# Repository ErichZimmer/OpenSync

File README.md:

# OpenSync
An open source synchronizer for the velocimetry of fluids using a Raspberry Pi microcontroller.

## Notice
The first batches of PCBs were ordered from JLCPCB for testing. If and when the PCBs pass testing and an initial PIV experiment is performed, the 1.0 milestone and initial release will be made along with a journal submission to HardwareX or JOH for publishment. Additionally, complete replication instructions will be included during the 1.0 milestone.

## Purpose
OpenSync is a simple and low-cost synchronizer based on microcontroller technology. Due to the intrinsic nature of microcontrollers compared to more advanced devices (e.g., field programmable gate arrays), sub-cycle accuracy and complex features that are typical of commercial propietary devices are not implemented. However, OpenSync remains sufficiently flexible and provides enough support for most users' needs when performing a PIV experiment. This is because OpenSync is a digital delay/pulse generator capable of having each output channel individually programmed. In adition to an all-microcontroller platform and a custom PCB, OpenSync devices provides a low-cost means to deterministic control of laboratory equipment.

## Basic Specs
 - **System Frequency**: 250 MHz (4 ns resolution)
 - **Output Channels**: 8
 - **Input Channels**: 2
 - **I/O Channel Voltage**: 3.3V or 5V @ high impedance

For a more detailed specification, please read the [datasheet](documents/datasheet/opensync_datasheet_markdown.md).

## Documentation
The complete documentation for OpenSync can be seen [here](https://erichzimmer.github.io/OpenSync/). Instructions to construct and use OpenSync are referenced [here](https://erichzimmer.github.io/OpenSync/users_guide/index.html). User's interested in the development process of OpenSync are kindly refered to the [SDLC documentation](documents/SDLC/README.md). There is a lot of information on the development process including some quirks from the pico microcontroller platform. Issues during construction or operation can be raised via GitHub issues to spread awareness.

## Acknowledgments
OpenSync thanks Dr. Ivan Nepomnyashchikh and Professor Alex Liberzon for spearheading open source, open hardware equipment for the OpenPIV project. The [original OpenPIV discussion](https://groups.google.com/g/openpiv-users/c/xi7qt28IGEE) helped initiate this project. Cost effective commercial PIV systems from [Optolution](https://optolution.com/en/) provided a strong inspiration to complete this project. Additionally, certain hardware from [MicroVec Pte Ltd](https://piv.com.sg/) was used as inspiration in earlier prototypes.

## Responsible AI
The use of large language models (or LLMs) within this project is disclosed under the [Responsible AI Disclosure](RESPONSIBLE_AI.md).

## TODO
- [x] Add timing plot utilities
- [x] Add device containerization for customization
- [x] Add the ability to change channel names
- [x] Add the ability to disable output channels (necessary?)
- [x] Add three internal timers that can be mapped to pulse sequences
- [x] Add the ability to count and skip external triggers (usefull for phase-locked stuff like rotor blades)
- [x] Add second external trigger and output port masking
- [x] Update firmware and software to reflect new design
- [x] Get the damn production PCB produced
- [ ] Lower cost of PCB further (currently up to ~$100 USD per board)
- [ ] Validate new PCB against an osciliscope (mostly power planes; outputs seem okay)
- [ ] Add video examples on YouTube

## References
 1. Radim Hošák, & Miroslav Ježek. (2018). Arbitrary digital pulse sequence generator with delay-loop timing. Review of Scientific Instruments, 89(4). https://doi.org/10.1063/1.5019685
 2. Scallon, A. (2017, June 18). Arduino TTL Pulse Generator and Controller. Optogenetics and Neural Engineering Core. https://optogeneticsandneuralengineeringcore.gitlab.io/ONECoreSite/projects/Arduino%20TTL%20Pulse%20Generator%20and%20Controller/
 3. Starkey, P. T., Turnbaugh, C., Miller, P., LeBlanc, K.-J., & Meyer, D. H. (2024). Experimental timing and control using microcontrollers. Review of Scientific Instruments, 95(10). https://doi.org/10.1063/5.0225550
 4. Stasicki, B. and Ehrenfried, K. and Dieterle, L. and Ludwikowski, K. and Raffel, M.  (2001) Advanced syncronization techniques for complex flow field investigations by means of PIV .    4th Intern. Symposium on Particle Image Velocimetry, Göttingen, Germany, September 17-19, 2001.  
    
## Licensing

| Licenses | OSHWA UID |
| --- | --- |
|  | N/A |

- Software: All firmware and software components are covered by the GNU GPLv3 license.
- Hardware: All hardware is covered by the CERN-OHL-S-v2 license.

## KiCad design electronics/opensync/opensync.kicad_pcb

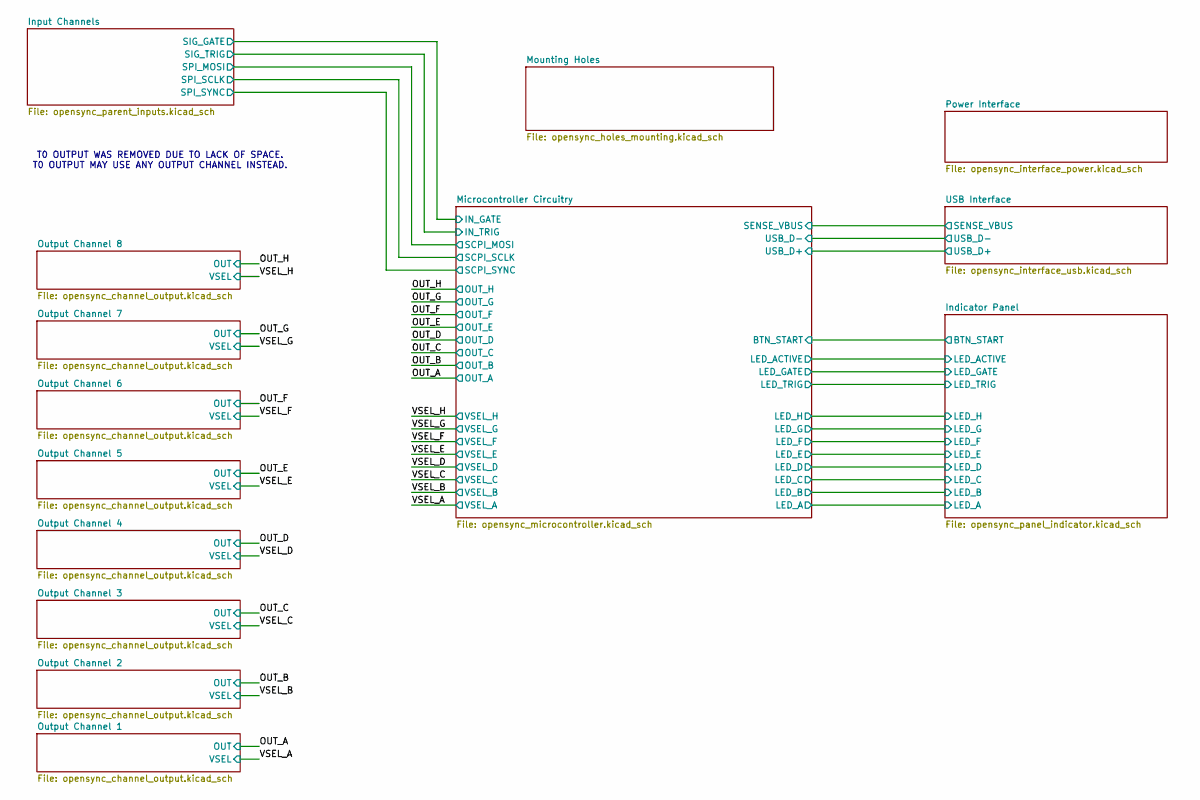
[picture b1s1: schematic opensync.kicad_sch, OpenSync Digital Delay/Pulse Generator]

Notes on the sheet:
T0 OUTPUT WAS REMOVED DUE TO LACK OF SPACE. T0 OUTPUT MAY USE ANY OUTPUT CHANNEL INSTEAD.

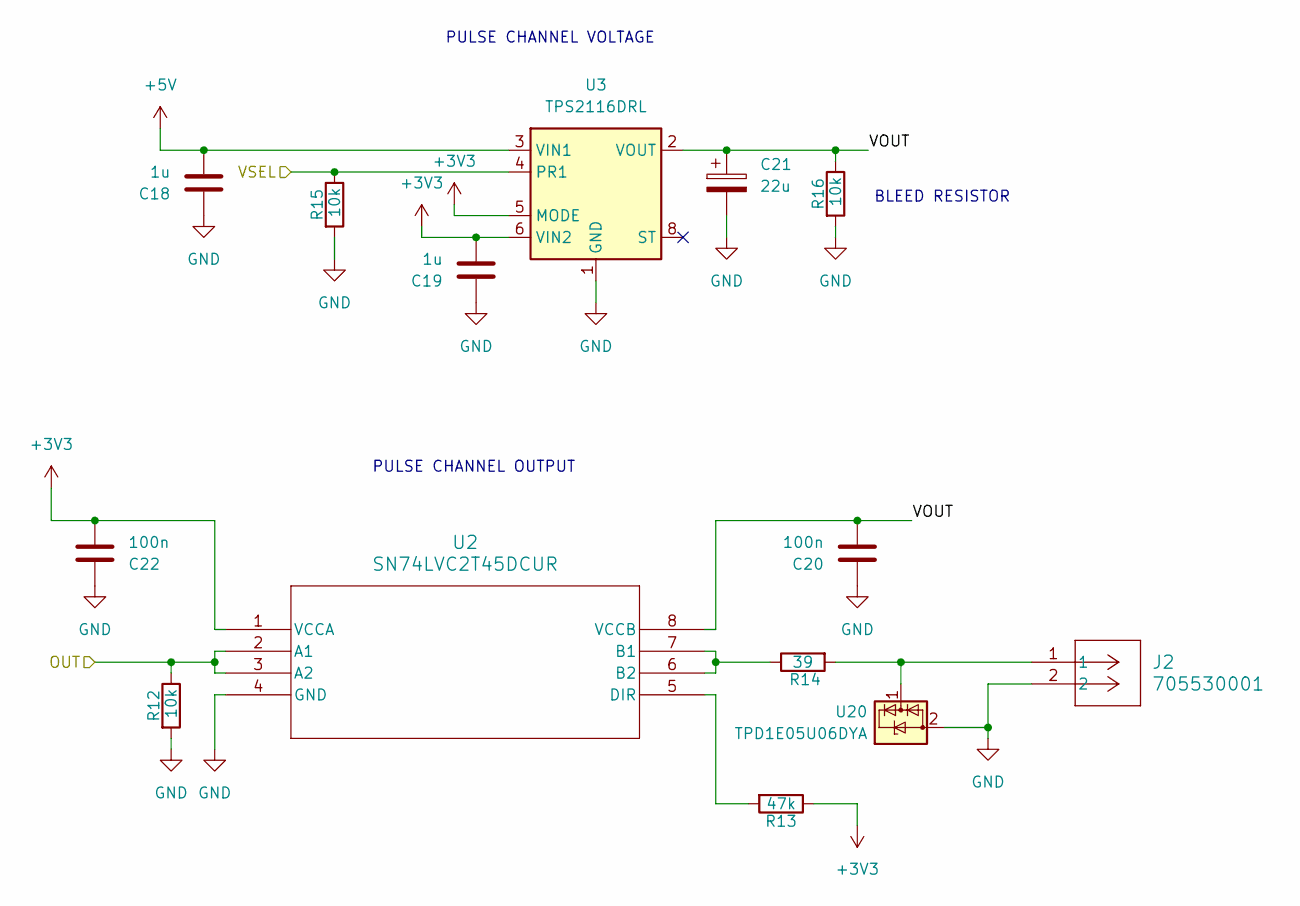
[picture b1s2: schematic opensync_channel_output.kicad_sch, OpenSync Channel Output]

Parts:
C18, C19: 1u; C_0603_1608Metric; voltage 25V; tolerance +/-10%; manufacturer_pn CGA3E1X7R1E105KT0Y0E; LCSC C76708
C20, C22: 100n; C_0402_1005Metric_small_pads; voltage 50V; tolerance ±10%; manufacturer_pn CGA2B3X7R1H104KT0Y0F; LCSC C343042
C21: 22u; CP_Elec_4x5.4; voltage 10V; tolerance +/-20%; manufacturer_pn 865060240001; LCSC C2164097
J2: 705530001; CONN_705530001_02_MOL; LCSC C564143
R12, R15: 10k; R_0402_1005Metric; tolerance ±1%; voltage 50V; manufacturer_pn CRCW040210K0FKED; LCSC C71617
R13: 47k; R_0402_1005Metric; tolerance ±1%; voltage 50V; manufacturer_pn CRCW040247K0FKED; LCSC C482184
R14: 39; R_0603_1608Metric; tolerance +/-1%; voltage 150 V; manufacturer_pn ERJUP3F39R0V; LCSC C544038
R16: 10k; R_0603_1608Metric; tolerance ±1%; voltage 75V; manufacturer_pn CRCW060310K0FKEA; LCSC C844918
U2: SN74LVC2T45DCUR; DCU8; voltage 1.65V~5.5V; manufacturer_pn SN74LVC2T45DCUR; LCSC C15741
U3: TPS2116DRL; SOT-583-8; manufacturer_pn TPS2116DRLR; LCSC C3235557
U20: TPD1E05U06DYA; D_SOD-523; manufacturer_pn TPD1E05U06DYAR; LCSC C3702980

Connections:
+3V3: C19.2, C22.2, R13.1, U2.1 (VCCA), U3.5 (MODE), U3.6 (VIN2); also elsewhere on the board
+5V: C18.2, U3.3 (VIN1); also elsewhere on the board
/OUT_A: R12.1, U2.2 (A1), U2.3 (A2); also elsewhere on the board
/Output Channel 1/VOUT: C20.2, C21.1, R16.1, U2.8 (VCCB), U3.2 (VOUT), U3.7 (VOUT)
/VSEL_A: R15.1, U3.4 (PR1); also elsewhere on the board
GND: C18.1, C19.1, C20.1, C21.2, C22.1, J2.2, R12.2, R15.2, R16.2, U2.4 (GND), U3.1 (GND), U20.2 (GND); also elsewhere on the board
unnamed: R14.1, U2.6 (B2), U2.7 (B1)
unnamed: R13.2, U2.5 (DIR)
unnamed: J2.1, R14.2, U20.1 (I/O)

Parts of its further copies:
C23, C24, C28, C29, C33, C34, C38, C39, C43, C44, C48, C49, C53, C54: 1u; C_0603_1608Metric; voltage 25V; tolerance +/-10%; manufacturer_pn CGA3E1X7R1E105KT0Y0E; LCSC C76708
C25, C27, C30, C32, C35, C37, C40, C42, C45, C47, C50, C52, C55, C57: 100n; C_0402_1005Metric_small_pads; voltage 50V; tolerance ±10%; manufacturer_pn CGA2B3X7R1H104KT0Y0F; LCSC C343042
C26, C31, C36, C41, C46, C51, C56: 22u; CP_Elec_4x5.4; voltage 10V; tolerance +/-20%; manufacturer_pn 865060240001; LCSC C2164097
J3, J4, J5, J6, J7, J8, J9: 705530001; CONN_705530001_02_MOL; LCSC C564143
R17, R20, R22, R25, R27, R30, R32, R35, R37, R40, R42, R45, R47, R50: 10k; R_0402_1005Metric; tolerance ±1%; voltage 50V; manufacturer_pn CRCW040210K0FKED; LCSC C71617
R18, R23, R28, R33, R38, R43, R48: 47k; R_0402_1005Metric; tolerance ±1%; voltage 50V; manufacturer_pn CRCW040247K0FKED; LCSC C482184
R19, R24, R29, R34, R39, R44, R49: 39; R_0603_1608Metric; tolerance +/-1%; voltage 150 V; manufacturer_pn ERJUP3F39R0V; LCSC C544038
R21, R26, R31, R36, R41, R46, R51: 10k; R_0603_1608Metric; tolerance ±1%; voltage 75V; manufacturer_pn CRCW060310K0FKEA; LCSC C844918
U4, U6, U8, U10, U12, U14, U16: SN74LVC2T45DCUR; DCU8; voltage 1.65V~5.5V; manufacturer_pn SN74LVC2T45DCUR; LCSC C15741
U5, U7, U9, U11, U13, U15, U17: TPS2116DRL; SOT-583-8; manufacturer_pn TPS2116DRLR; LCSC C3235557
U21, U22, U23, U24, U25, U26, U27: TPD1E05U06DYA; D_SOD-523; manufacturer_pn TPD1E05U06DYAR; LCSC C3702980

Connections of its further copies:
+3V3: C24.2, C27.2, C29.2, C32.2, C34.2, C37.2, C39.2, C42.2, C44.2, C47.2, C49.2, C52.2, C54.2, C57.2, R18.1, R23.1, R28.1, R33.1, R38.1, R43.1, R48.1, U4.1 (VCCA), U5.5 (MODE), U5.6 (VIN2), U6.1 (VCCA), U7.5 (MODE), U7.6 (VIN2), U8.1 (VCCA), U9.5 (MODE), U9.6 (VIN2), U10.1 (VCCA), U11.5 (MODE), U11.6 (VIN2), U12.1 (VCCA), U13.5 (MODE), U13.6 (VIN2), U14.1 (VCCA), U15.5 (MODE), U15.6 (VIN2), U16.1 (VCCA), U17.5 (MODE), U17.6 (VIN2); also elsewhere on the board
+5V: C23.2, C28.2, C33.2, C38.2, C43.2, C48.2, C53.2, U5.3 (VIN1), U7.3 (VIN1), U9.3 (VIN1), U11.3 (VIN1), U13.3 (VIN1), U15.3 (VIN1), U17.3 (VIN1); also elsewhere on the board
/OUT_B: R17.1, U4.2 (A1), U4.3 (A2); also elsewhere on the board
/OUT_C: R22.1, U6.2 (A1), U6.3 (A2); also elsewhere on the board
/OUT_D: R27.1, U8.2 (A1), U8.3 (A2); also elsewhere on the board
/OUT_E: R32.1, U10.2 (A1), U10.3 (A2); also elsewhere on the board
/OUT_F: R37.1, U12.2 (A1), U12.3 (A2); also elsewhere on the board
/OUT_G: R42.1, U14.2 (A1), U14.3 (A2); also elsewhere on the board
/OUT_H: R47.1, U16.2 (A1), U16.3 (A2); also elsewhere on the board
/Output Channel 2/VOUT: C25.2, C26.1, R21.1, U4.8 (VCCB), U5.2 (VOUT), U5.7 (VOUT)
/Output Channel 3/VOUT: C30.2, C31.1, R26.1, U6.8 (VCCB), U7.2 (VOUT), U7.7 (VOUT)
/Output Channel 4/VOUT: C35.2, C36.1, R31.1, U8.8 (VCCB), U9.2 (VOUT), U9.7 (VOUT)
/Output Channel 5/VOUT: C40.2, C41.1, R36.1, U10.8 (VCCB), U11.2 (VOUT), U11.7 (VOUT)
/Output Channel 6/VOUT: C45.2, C46.1, R41.1, U12.8 (VCCB), U13.2 (VOUT), U13.7 (VOUT)
/Output Channel 7/VOUT: C50.2, C51.1, R46.1, U14.8 (VCCB), U15.2 (VOUT), U15.7 (VOUT)
/Output Channel 8/VOUT: C55.2, C56.1, R51.1, U16.8 (VCCB), U17.2 (VOUT), U17.7 (VOUT)
/VSEL_B: R20.1, U5.4 (PR1); also elsewhere on the board
/VSEL_C: R25.1, U7.4 (PR1); also elsewhere on the board
/VSEL_D: R30.1, U9.4 (PR1); also elsewhere on the board
/VSEL_E: R35.1, U11.4 (PR1); also elsewhere on the board
/VSEL_F: R40.1, U13.4 (PR1); also elsewhere on the board
/VSEL_G: R45.1, U15.4 (PR1); also elsewhere on the board
/VSEL_H: R50.1, U17.4 (PR1); also elsewhere on the board
GND: C23.1, C24.1, C25.1, C26.2, C27.1, C28.1, C29.1, C30.1, C31.2, C32.1, C33.1, C34.1, C35.1, C36.2, C37.1, C38.1, C39.1, C40.1, C41.2, C42.1, C43.1, C44.1, C45.1, C46.2, C47.1, C48.1, C49.1, C50.1, C51.2, C52.1, C53.1, C54.1, C55.1, C56.2, C57.1, J3.2, J4.2, J5.2, J6.2, J7.2, J8.2, J9.2, R17.2, R20.2, R21.2, R22.2, R25.2, R26.2, R27.2, R30.2, R31.2, R32.2, R35.2, R36.2, R37.2, R40.2, R41.2, R42.2, R45.2, R46.2, R47.2, R50.2, R51.2, U4.4 (GND), U5.1 (GND), U6.4 (GND), U7.1 (GND), U8.4 (GND), U9.1 (GND), U10.4 (GND), U11.1 (GND), U12.4 (GND), U13.1 (GND), U14.4 (GND), U15.1 (GND), U16.4 (GND), U17.1 (GND), U21.2 (GND), U22.2 (GND), U23.2 (GND), U24.2 (GND), U25.2 (GND), U26.2 (GND), U27.2 (GND); also elsewhere on the board
unnamed: R19.1, U4.6 (B2), U4.7 (B1)
unnamed: R18.2, U4.5 (DIR)
unnamed: R24.1, U6.6 (B2), U6.7 (B1)
unnamed: R23.2, U6.5 (DIR)
unnamed: R29.1, U8.6 (B2), U8.7 (B1)
unnamed: R28.2, U8.5 (DIR)
unnamed: R34.1, U10.6 (B2), U10.7 (B1)
unnamed: R33.2, U10.5 (DIR)
unnamed: R39.1, U12.6 (B2), U12.7 (B1)
unnamed: R38.2, U12.5 (DIR)
unnamed: R44.1, U14.6 (B2), U14.7 (B1)
unnamed: R43.2, U14.5 (DIR)
unnamed: R49.1, U16.6 (B2), U16.7 (B1)
unnamed: R48.2, U16.5 (DIR)
unnamed: J3.1, R19.2, U21.1 (I/O)
unnamed: J4.1, R24.2, U22.1 (I/O)
unnamed: J5.1, R29.2, U23.1 (I/O)
unnamed: J6.1, R34.2, U24.1 (I/O)
unnamed: J7.1, R39.2, U25.1 (I/O)
unnamed: J8.1, R44.2, U26.1 (I/O)
unnamed: J9.1, R49.2, U27.1 (I/O)

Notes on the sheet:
BLEED RESISTOR
PULSE CHANNEL OUTPUT
PULSE CHANNEL VOLTAGE

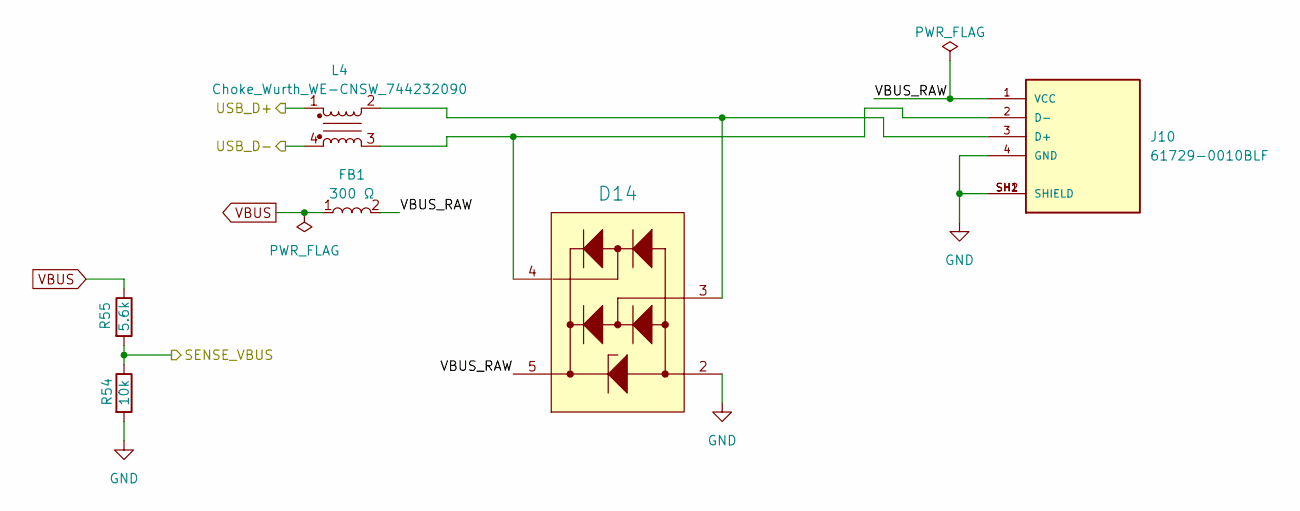
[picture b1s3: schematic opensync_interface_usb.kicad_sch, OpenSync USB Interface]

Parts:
D14: 5V; WE-TVS_SOT23-5L; Manufacturer Part Number 824011; LCSC C5341668
FB1: 0603_W2.6_742792641; FB_Wurth_WE-CBF-0603_W2.6; tolerance ±25%; Part Number 742792641; LCSC C2649308
J10: 61729-0010BLF; AMPHENOL_61729-0010BLF; PARTREV AD; LCSC C598579
L4: Choke_Wurth_WE-CNSW_744232090; L_CommonMode_Wurth_WE-CNSW-1206; voltage 50V; manufacturer_pn 744232090; LCSC C2649327
R54: 10k; R_0603_1608Metric; tolerance ±1%; voltage 75V; manufacturer_pn CRCW060310K0FKEA; LCSC C844918
R55: 5.6k; R_0603_1608Metric; tolerance ±1%; voltage 75V; manufacturer_pn CRCW06035K60FKEA; LCSC C844799

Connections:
/Microcontroller Circuitry/SENSE_VBUS: R54.1, R55.2; also elsewhere on the board
/Microcontroller Circuitry/USB_D+: L4.1; also elsewhere on the board
/Microcontroller Circuitry/USB_D-: L4.4; also elsewhere on the board
/USB Interface/VBUS_RAW: D14.5 (VDD), FB1.2, J10.1 (VCC)
GND: D14.2 (GND), J10.4 (GND), J10.SH1 (SHIELD), J10.SH2 (SHIELD), R54.2; also elsewhere on the board
unnamed: D14.3 (I/O_1), J10.3 (D+), L4.2
unnamed: D14.4 (I/O_2), J10.2 (D-), L4.3
VBUS: FB1.1, R55.1; also elsewhere on the board

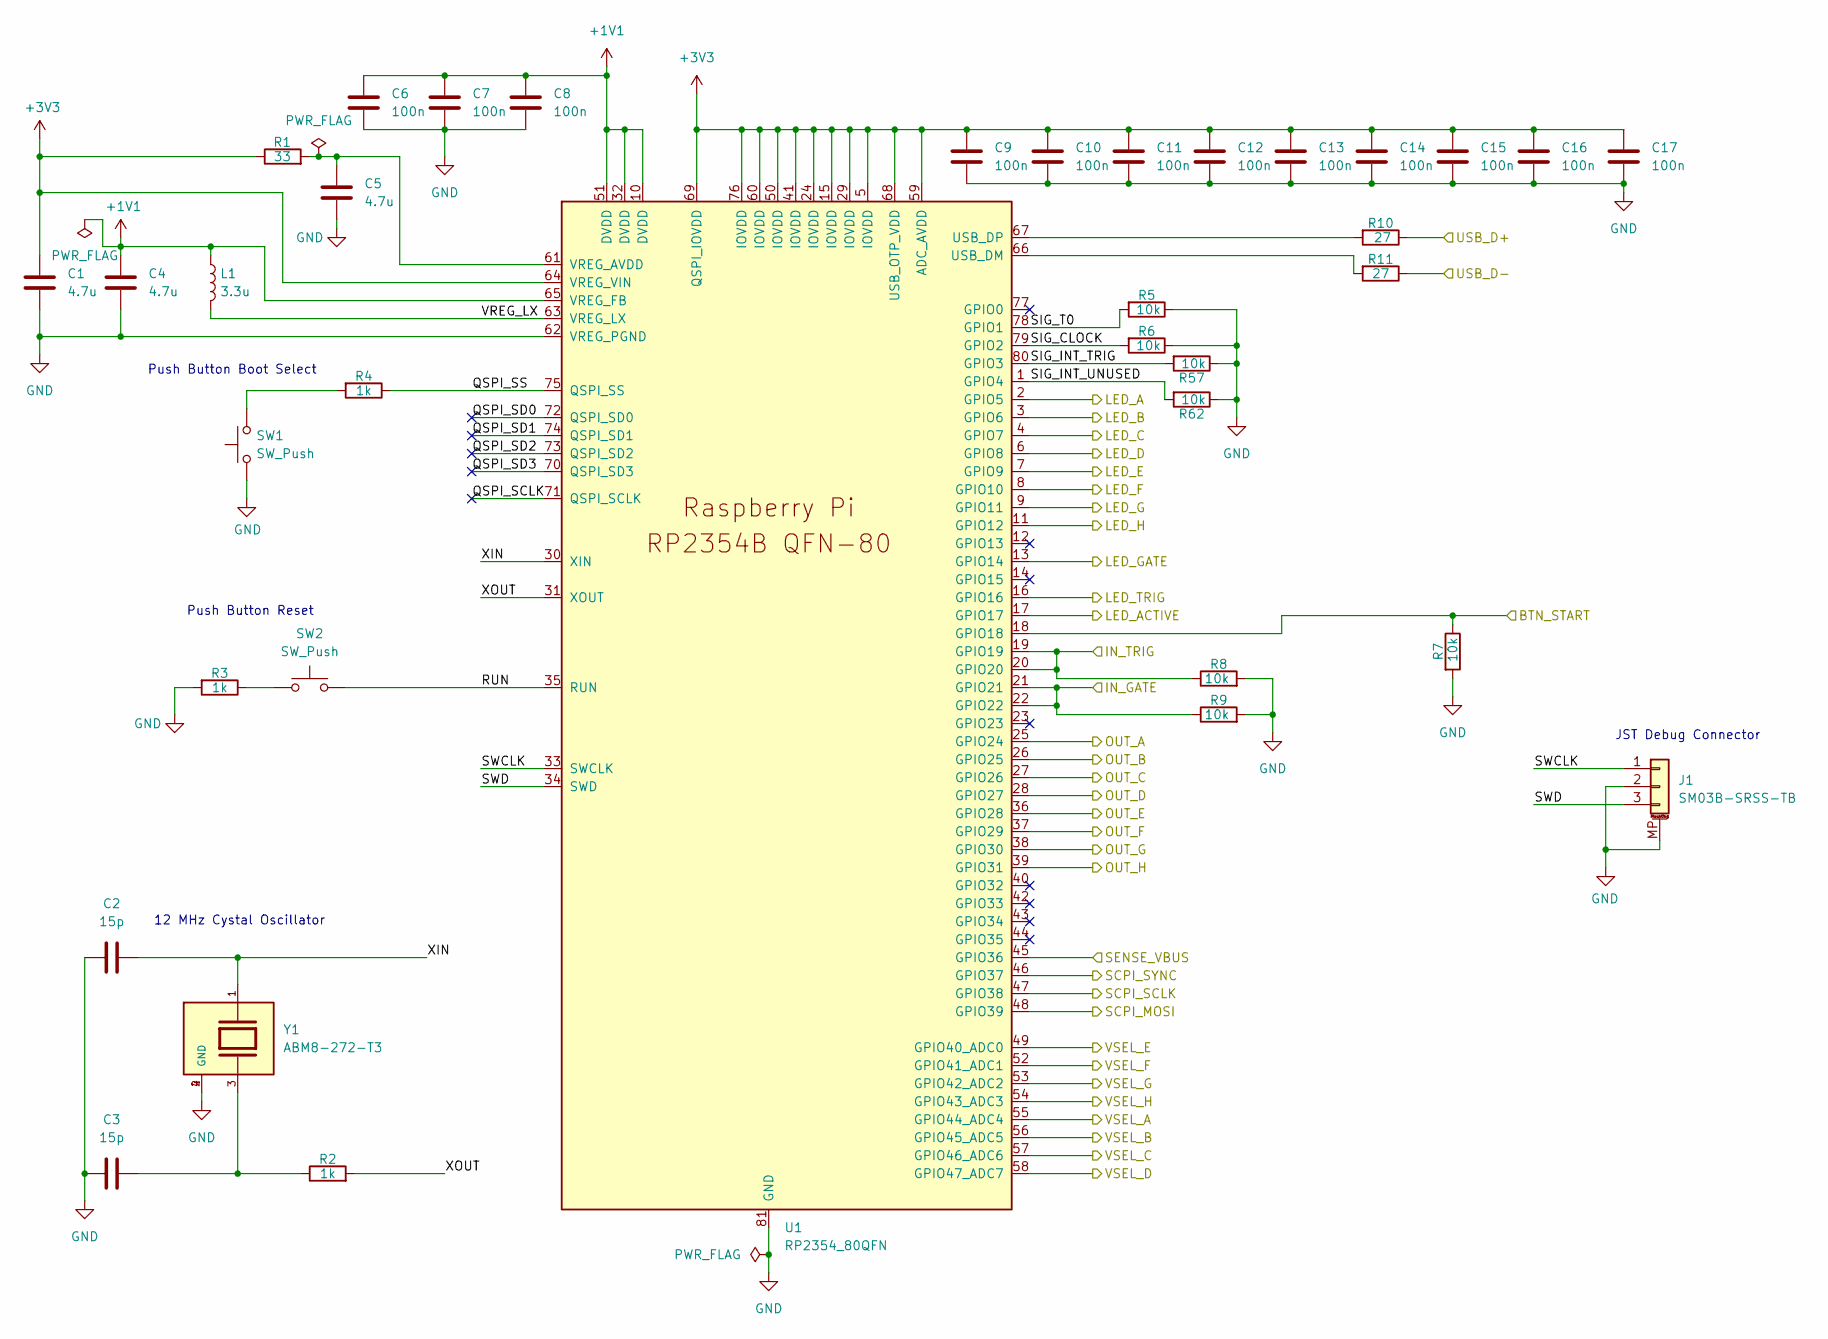
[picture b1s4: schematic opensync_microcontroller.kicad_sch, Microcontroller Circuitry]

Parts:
C1, C4, C5: 4.7u; C_0402_1005Metric_small_pads; voltage 10V; tolerance ±10%; manufacturer_pn C1005X5R1A475KTJ00E; LCSC C342983
C2, C3: 15p; C_0402_1005Metric_small_pads; voltage 50V; tolerance ±5%; manufacturer_pn CGA2B2C0G1H150JT0Y0F; LCSC C338103
C6, C7, C8, C9, C10, C11, C12, C13, C14, C15, C16, C17: 100n; C_0402_1005Metric_small_pads; voltage 50V; tolerance ±10%; manufacturer_pn CGA2B3X7R1H104KT0Y0F; LCSC C343042
J1: SM03B-SRSS-TB; JST_SH_SM03B-SRSS-TB_1x03-1MP_P1.00mm_Horizontal; voltage 50V; manufacturer_pn SM03B-SRSS-TB(LF)(SN); LCSC C160403
L1: 3.3u; L_pol_2016; manufacturer_pn AOTA-B201610S3R3-101-T; LCSC C42411119
R1: 33; R_0402_1005Metric; tolerance ±1%; voltage 50 V; manufacturer_pn CRCW040233R0FKEDC; LCSC C844506
R2, R3, R4: 1k; R_0402_1005Metric; tolerance ±1%; voltage 50V; manufacturer_pn CRCW04021K00FKEDHP; LCSC C313354
R5, R6, R7, R8, R9, R57, R62: 10k; R_0402_1005Metric; tolerance ±1%; voltage 50V; manufacturer_pn CRCW040210K0FKED; LCSC C71617
R10, R11: 27; R_0402_1005Metric; tolerance +/-1%; voltage 50 V; manufacturer_pn CRCW040227R0FKEDC; LCSC C4162575
SW1, SW2: SW_Push; SW_Push_1P1T_NO_Vertical_Wuerth_434133025816; voltage 16V; manufacturer_pn 434133025816; LCSC C5504987
U1: RP2354_80QFN; RP2350-QFN-80-1EP_10x10_P0.4mm_EP3.4x3.4mm_ThermalVias; manufacturer_pn RP2354B; LCSC C39843328
Y1: ABM8-272-T3; XTAL_ABM8-272-T3; PARTREV 07-29-20; LCSC C20625731

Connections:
+1V1: C4.1, C6.1, C7.1, C8.1, L1.1, U1.10 (DVDD), U1.32 (DVDD), U1.51 (DVDD), U1.65 (VREG_FB)
+3V3: C1.1, C9.1, C10.1, C11.1, C12.1, C13.1, C14.1, C15.1, C16.1, C17.1, R1.1, U1.5 (IOVDD), U1.15 (IOVDD), U1.24 (IOVDD), U1.29 (IOVDD), U1.41 (IOVDD), U1.50 (IOVDD), U1.59 (ADC_AVDD), U1.60 (IOVDD), U1.64 (VREG_VIN), U1.68 (USB_OTP_VDD), U1.69 (QSPI_IOVDD), U1.76 (IOVDD); also elsewhere on the board
/Indicator Panel/BTN_START: R7.1, U1.18 (GPIO18); also elsewhere on the board
/Indicator Panel/LED_A: U1.2 (GPIO5); also elsewhere on the board
/Indicator Panel/LED_ACTIVE: U1.17 (GPIO17); also elsewhere on the board
/Indicator Panel/LED_B: U1.3 (GPIO6); also elsewhere on the board
/Indicator Panel/LED_C: U1.4 (GPIO7); also elsewhere on the board
/Indicator Panel/LED_D: U1.6 (GPIO8); also elsewhere on the board
/Indicator Panel/LED_E: U1.7 (GPIO9); also elsewhere on the board
/Indicator Panel/LED_F: U1.8 (GPIO10); also elsewhere on the board
/Indicator Panel/LED_G: U1.9 (GPIO11); also elsewhere on the board
/Indicator Panel/LED_GATE: U1.13 (GPIO14); also elsewhere on the board
/Indicator Panel/LED_H: U1.11 (GPIO12); also elsewhere on the board
/Indicator Panel/LED_TRIG: U1.16 (GPIO16); also elsewhere on the board
/Input Channels/SIG_GATE: R9.1, U1.21 (GPIO21), U1.22 (GPIO22); also elsewhere on the board
/Input Channels/SIG_TRIG: R8.1, U1.19 (GPIO19), U1.20 (GPIO20); also elsewhere on the board
/Input Channels/SPI_MOSI: U1.48 (GPIO39); also elsewhere on the board
/Input Channels/SPI_SCLK: U1.47 (GPIO38); also elsewhere on the board
/Input Channels/SPI_SYNC: U1.46 (GPIO37); also elsewhere on the board
/Microcontroller Circuitry/QSPI_SCLK: U1.71 (QSPI_SCLK)
/Microcontroller Circuitry/QSPI_SD0: U1.72 (QSPI_SD0)
/Microcontroller Circuitry/QSPI_SD1: U1.74 (QSPI_SD1)
/Microcontroller Circuitry/QSPI_SD2: U1.73 (QSPI_SD2)
/Microcontroller Circuitry/QSPI_SD3: U1.70 (QSPI_SD3)
/Microcontroller Circuitry/QSPI_SS: R4.1, U1.75 (QSPI_SS)
/Microcontroller Circuitry/RUN: SW2.2, U1.35 (RUN)
/Microcontroller Circuitry/SENSE_VBUS: U1.45 (GPIO36); also elsewhere on the board
/Microcontroller Circuitry/SIG_CLOCK: R6.2, U1.79 (GPIO2)
/Microcontroller Circuitry/SIG_INT_TRIG: R57.2, U1.80 (GPIO3)
/Microcontroller Circuitry/SIG_INT_UNUSED: R62.2, U1.1 (GPIO4)
/Microcontroller Circuitry/SIG_T0: R5.2, U1.78 (GPIO1)
/Microcontroller Circuitry/SWCLK: J1.1, U1.33 (SWCLK)
/Microcontroller Circuitry/SWD: J1.3, U1.34 (SWD)
/Microcontroller Circuitry/USB_D+: R10.1; also elsewhere on the board
/Microcontroller Circuitry/USB_D-: R11.1; also elsewhere on the board
/Microcontroller Circuitry/VREG_LX: L1.2, U1.63 (VREG_LX)
/Microcontroller Circuitry/XIN: C2.2, U1.30 (XIN), Y1.1
/Microcontroller Circuitry/XOUT: R2.2, U1.31 (XOUT)
/OUT_A: U1.25 (GPIO24); also elsewhere on the board
/OUT_B: U1.26 (GPIO25); also elsewhere on the board
/OUT_C: U1.27 (GPIO26); also elsewhere on the board
/OUT_D: U1.28 (GPIO27); also elsewhere on the board
/OUT_E: U1.36 (GPIO28); also elsewhere on the board
/OUT_F: U1.37 (GPIO29); also elsewhere on the board
/OUT_G: U1.38 (GPIO30); also elsewhere on the board
/OUT_H: U1.39 (GPIO31); also elsewhere on the board
/VSEL_A: U1.55 (GPIO44_ADC4); also elsewhere on the board
/VSEL_B: U1.56 (GPIO45_ADC5); also elsewhere on the board
/VSEL_C: U1.57 (GPIO46_ADC6); also elsewhere on the board
/VSEL_D: U1.58 (GPIO47_ADC7); also elsewhere on the board
/VSEL_E: U1.49 (GPIO40_ADC0); also elsewhere on the board
/VSEL_F: U1.52 (GPIO41_ADC1); also elsewhere on the board
/VSEL_G: U1.53 (GPIO42_ADC2); also elsewhere on the board
/VSEL_H: U1.54 (GPIO43_ADC3); also elsewhere on the board
GND: C1.2, C2.1, C3.1, C4.2, C5.2, C6.2, C7.2, C8.2, C9.2, C10.2, C11.2, C12.2, C13.2, C14.2, C15.2, C16.2, C17.2, J1.2, J1.MP (MountPin), R3.2, R5.1, R6.1, R7.2, R8.2, R9.2, R57.1, R62.1, SW1.1, U1.62 (VREG_PGND), U1.81 (GND), Y1.2 (GND), Y1.4 (GND); also elsewhere on the board
unnamed: C3.2, R2.1, Y1.3
unnamed: R3.1, SW2.1
unnamed: R4.2, SW1.2
unnamed: R11.2, U1.66 (USB_DM)
unnamed: R10.2, U1.67 (USB_DP)
unnamed: C5.1, R1.2, U1.61 (VREG_AVDD)

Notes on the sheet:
Push Button Boot Select
JST Debug Connector
12 MHz Cystal Oscillator
Push Button Reset

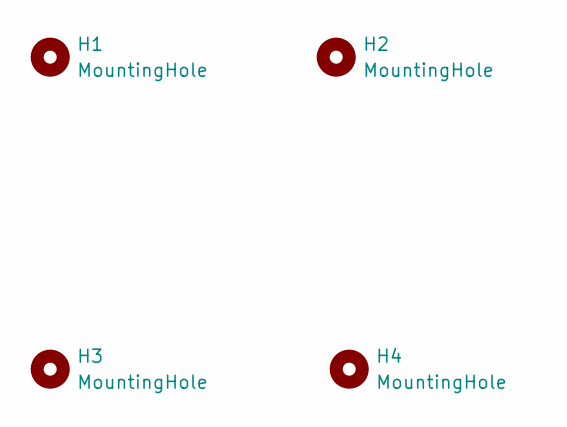
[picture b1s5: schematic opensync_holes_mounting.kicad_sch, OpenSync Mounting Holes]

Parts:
H1, H2, H3, H4: MountingHole; MountingHole_3.2mm_M3_ISO7380

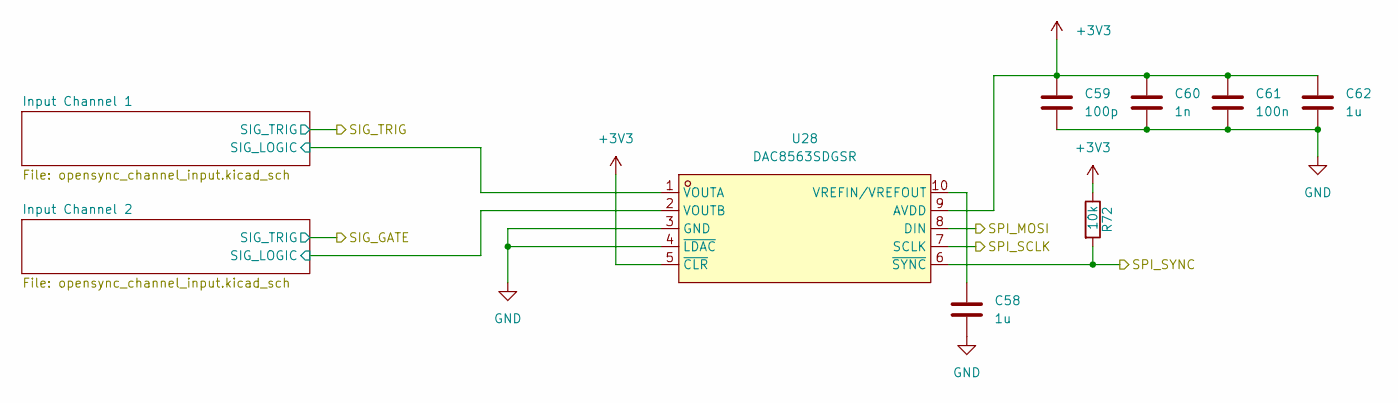
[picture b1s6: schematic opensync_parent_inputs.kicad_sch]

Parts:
C58, C62: 1u; C_0603_1608Metric; LCSC C76708
C59: 100p; C_0402_1005Metric_small_pads; LCSC C281750
C60: 1n; C_0402_1005Metric_small_pads; LCSC C76704
C61: 100n; C_0402_1005Metric_small_pads; LCSC C343042
R72: 10k; R_0402_1005Metric; tolerance ±1%; voltage 50V; manufacturer_pn CRCW040210K0FKED; LCSC C71617
U28: DAC8563SDGSR; VSSOP-10_L3.0-W3.0-P0.50-LS4.9-BL; MPN DAC8563SDGSR; LCSC C1554729

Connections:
+3V3: C59.1, C60.1, C61.1, C62.1, R72.1, U28.5 (~CLR), U28.9 (AVDD); also elsewhere on the board
/Input Channels/Input Channel 1/SIG_LOGIC: U28.1 (VOUTA); also elsewhere on the board
/Input Channels/Input Channel 2/SIG_LOGIC: U28.2 (VOUTB); also elsewhere on the board
/Input Channels/SPI_MOSI: U28.8 (DIN); also elsewhere on the board
/Input Channels/SPI_SCLK: U28.7 (SCLK); also elsewhere on the board
/Input Channels/SPI_SYNC: R72.2, U28.6 (~SYNC); also elsewhere on the board
GND: C58.2, C59.2, C60.2, C61.2, C62.2, U28.3 (GND), U28.4 (~LDAC); also elsewhere on the board
unnamed: C58.1, U28.10 (VREFIN/VREFOUT)

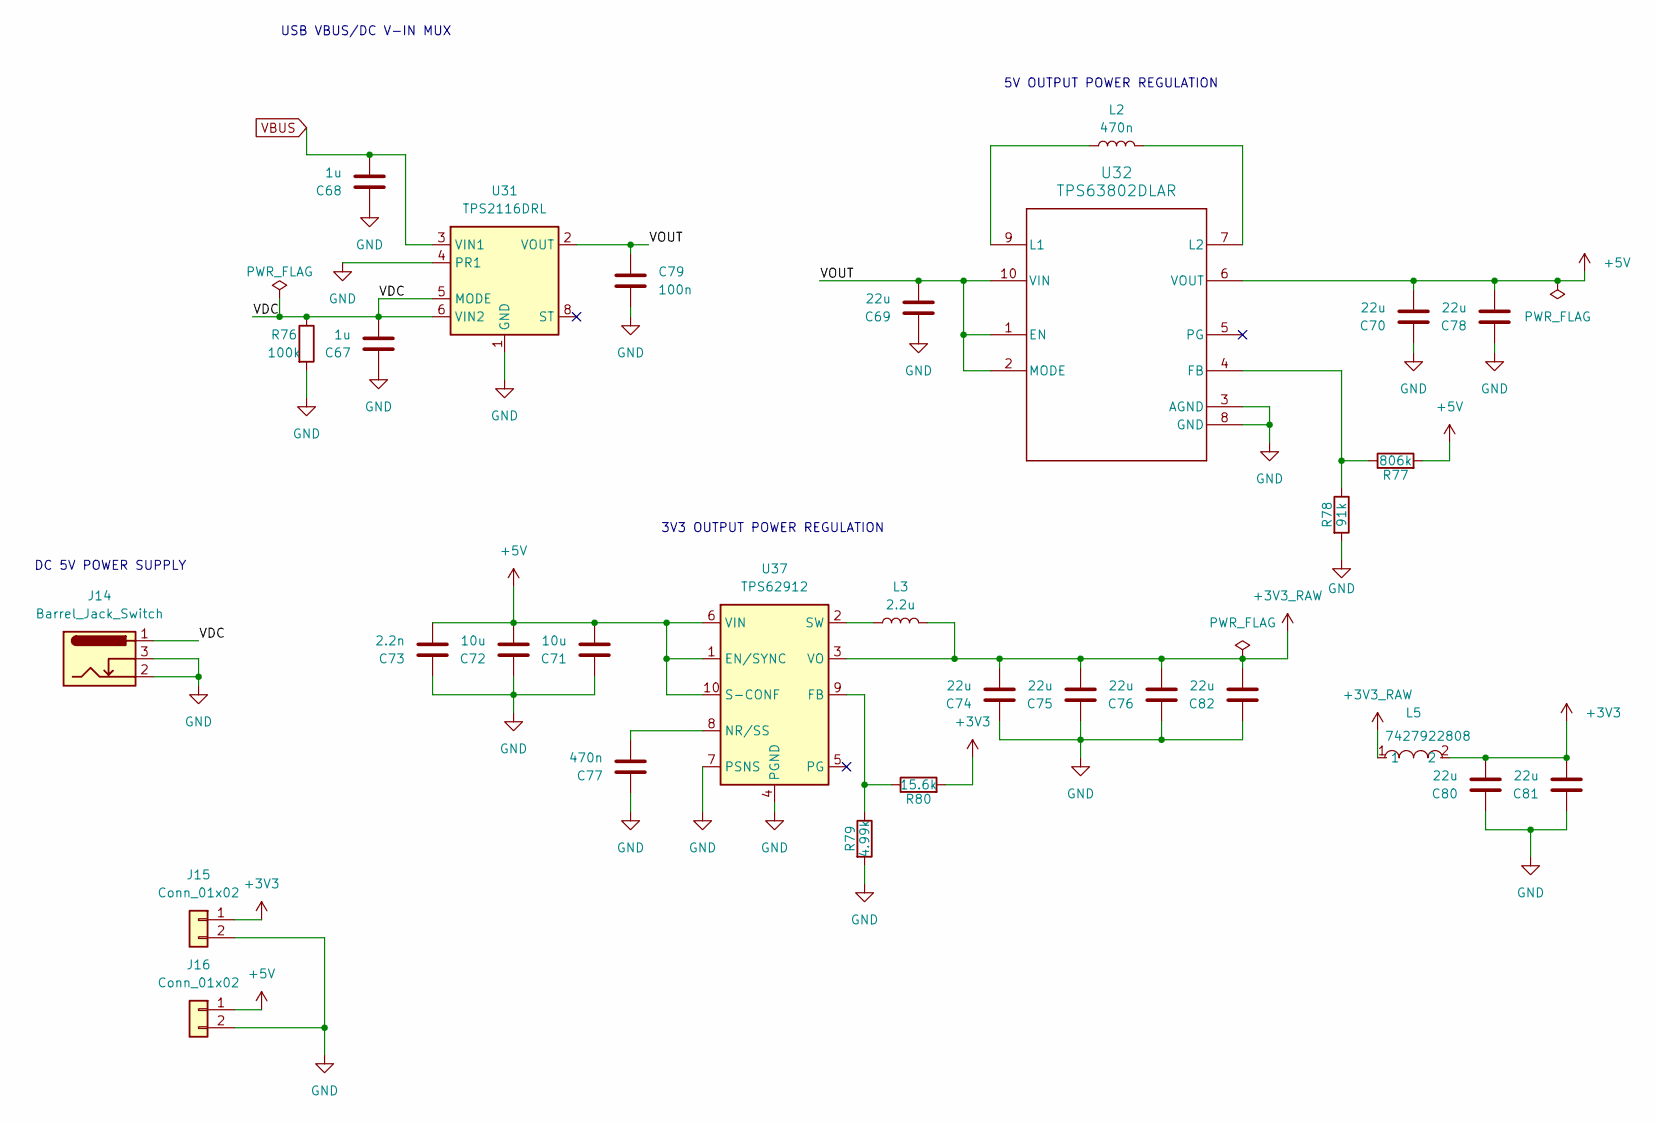
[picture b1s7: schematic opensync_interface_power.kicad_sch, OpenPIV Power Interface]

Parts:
C67, C68: 1u; C_0603_1608Metric; voltage 25V; tolerance +/-10%; manufacturer_pn CGA3E1X7R1E105KT0Y0E; LCSC C76708
C69, C70, C74, C75, C76, C78, C80, C81, C82: 22u; C_0805_2012Metric; voltage 10V; tolerance ±20%; manufacturer_pn C2012X7S1A226MT000E; LCSC C342717
C71, C72: 10u; C_0805_2012Metric; voltage 35V; tolerance ±10%; manufacturer_pn C2012X5R1V106KT000E; LCSC C342722
C73: 2.2n; C_0402_1005Metric_small_pads; voltage 50V; tolerance +/-10%; manufacturer_pn CGA2B2X7R1H222KT0Y0F; LCSC C338081
C77: 470n; C_0402_1005Metric_small_pads; voltage 16V; tolerance +/-10%; manufacturer_pn CGA2B1X7S1C474KT000F; LCSC C432936
C79: 100n; C_0402_1005Metric_small_pads; voltage 50V; tolerance ±10%; manufacturer_pn CGA2B3X7R1H104KT0Y0F; LCSC C343042
J14: Barrel_Jack_Switch; BarrelJack_Wuerth_6941xx301002; manufacturer_pn 694106301002; LCSC C5441017
J15, J16: Conn_01x02; CONN-TH_705430001; LCSC C127361
L2: 470n; L_TDK_TMS252012ALM; tolerance ±20%; manufacturer_pn TMS252012ALM-R47MTAA; LCSC C24296304
L3: 2.2u; L_Wuerth_MAPI-4020; tolerance ±20%; manufacturer_pn 74438356022; LCSC C5521727
L5: 7427922808; L0603; MPN 7427922808; LCSC C2661810
R76: 100k; R_0402_1005Metric; tolerance ±1%; voltage 50V; manufacturer_pn CRCW0402100KFKED; LCSC C481918
R77: 806k; R_0402_1005Metric; tolerance +/-1%; voltage 50 V; manufacturer_pn CRCW0402806KFKED; LCSC C2076627
R78: 91k; R_0402_1005Metric; tolerance +/-1%; voltage 50 V; manufacturer_pn CRCW040291K0FKED; LCSC C2086333
R79: 4.99k; R_0402_1005Metric; tolerance +/-1%; voltage 50 V; manufacturer_pn CRCW04024K99FKEE; LCSC C4010684
R80: 15.6k; R_0402_1005Metric; tolerance +/-0.1%; voltage 50 V; manufacturer_pn TNPW040215K6BEED; LCSC C2075329
U31: TPS2116DRL; SOT-583-8; manufacturer_pn TPS2116DRLR; LCSC C3235557
U32: TPS63802DLAR; DLA0010A; voltage 1.3V~5.5V; manufacturer_pn TPS63802DLAR; LCSC C2845237
U37: TPS62912; Texas_RPU0010A_VQFN-HR-10_2x2mm_P0.5mm; voltage 3V~17V; manufacturer_pn TPS62912RPUR; LCSC C3198056

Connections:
+3V3: C80.2, C81.2, J15.1, L5.2, R80.2; also elsewhere on the board
+3V3_RAW: C74.2, C75.2, C76.2, C82.2, L3.2, L5.1, U37.3 (VO)
+5V: C70.2, C71.2, C72.2, C73.2, C78.2, J16.1, R77.2, U32.6 (VOUT), U37.1 (EN/SYNC), U37.6 (VIN), U37.10 (S-CONF); also elsewhere on the board
/Power Interface/VDC: C67.2, J14.1, R76.1, U31.5 (MODE), U31.6 (VIN2)
/Power Interface/VOUT: C69.2, C79.1, U31.2 (VOUT), U31.7 (VOUT), U32.1 (EN), U32.2 (MODE), U32.10 (VIN)
GND: C67.1, C68.1, C69.1, C70.1, C71.1, C72.1, C73.1, C74.1, C75.1, C76.1, C77.1, C78.1, C79.2, C80.1, C81.1, C82.1, J14.2, J14.3, J15.2, J16.2, R76.2, R78.2, R79.2, U31.1 (GND), U31.4 (PR1), U32.3 (AGND), U32.8 (GND), U37.4 (PGND), U37.7 (PSNS); also elsewhere on the board
unnamed: R77.1, R78.1, U32.4 (FB)
unnamed: L2.1, U32.9 (L1)
unnamed: L2.2, U32.7 (L2)
unnamed: R79.1, R80.1, U37.9 (FB)
unnamed: C77.2, U37.8 (NR/SS)
unnamed: L3.1, U37.2 (SW)
VBUS: C68.2, U31.3 (VIN1); also elsewhere on the board

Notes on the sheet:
3V3 OUTPUT POWER REGULATION
DC 5V POWER SUPPLY
USB VBUS/DC V-IN MUX
5V OUTPUT POWER REGULATION

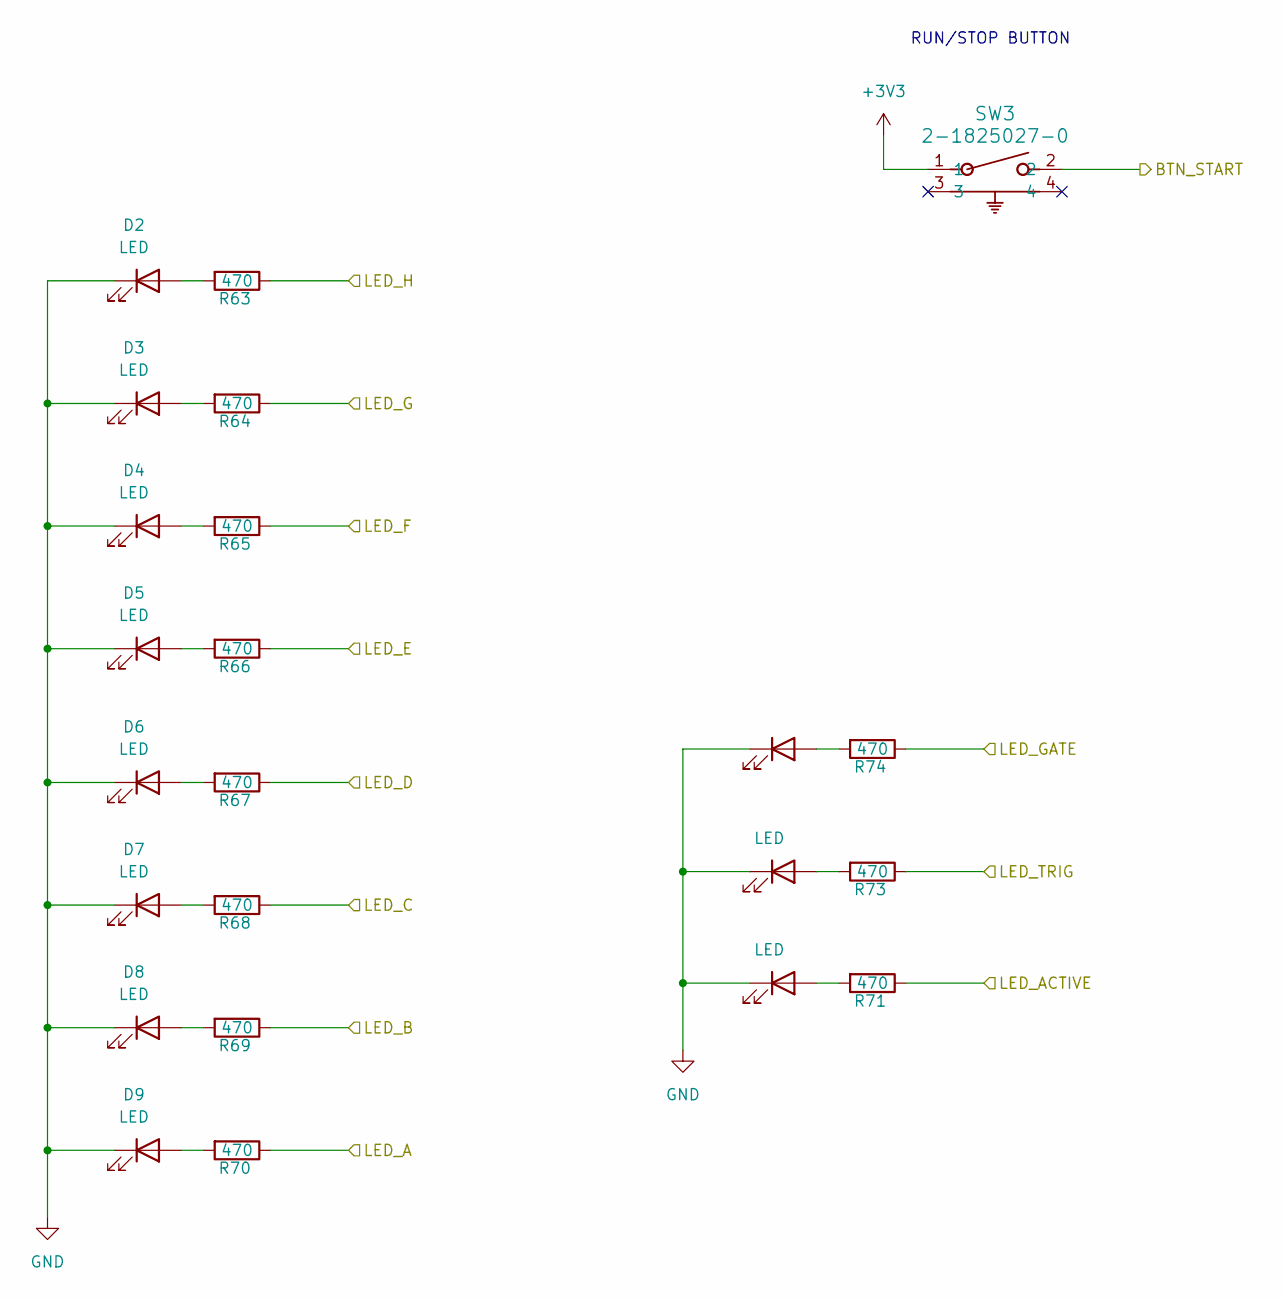
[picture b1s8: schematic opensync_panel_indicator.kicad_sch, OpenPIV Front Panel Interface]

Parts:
D2, D3, D4, D5, D6, D7, D8, D9, D10, D12, D13: LED; LED-SMD_L4.0-W3.6_A67F-U2BA-1-3A4B-30-R33; manufacturer_pn XL-C4040UGC; LCSC C7545687
R63, R64, R65, R66, R67, R68, R69, R70, R71, R73, R74: 470; R_0603_1608Metric; tolerance ±1%; voltage 75V; manufacturer_pn CRCW0603470RFKEA; LCSC C844786
SW3: 2-1825027-0; SW2_1825027-G_TEC; voltage 24V; manufacturer_pn 2-1825027-0; LCSC C590206

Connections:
+3V3: SW3.1; also elsewhere on the board
/Indicator Panel/BTN_START: SW3.2; also elsewhere on the board
/Indicator Panel/LED_A: R70.1; also elsewhere on the board
/Indicator Panel/LED_ACTIVE: R71.1; also elsewhere on the board
/Indicator Panel/LED_B: R69.1; also elsewhere on the board
/Indicator Panel/LED_C: R68.1; also elsewhere on the board
/Indicator Panel/LED_D: R67.1; also elsewhere on the board
/Indicator Panel/LED_E: R66.1; also elsewhere on the board
/Indicator Panel/LED_F: R65.1; also elsewhere on the board
/Indicator Panel/LED_G: R64.1; also elsewhere on the board
/Indicator Panel/LED_GATE: R74.1; also elsewhere on the board
/Indicator Panel/LED_H: R63.1; also elsewhere on the board
/Indicator Panel/LED_TRIG: R73.1; also elsewhere on the board
GND: D2.1 (K), D3.1 (K), D4.1 (K), D5.1 (K), D6.1 (K), D7.1 (K), D8.1 (K), D9.1 (K), D10.1 (K), D12.1 (K), D13.1 (K); also elsewhere on the board
unnamed: D2.2 (A), R63.2
unnamed: D3.2 (A), R64.2
unnamed: D4.2 (A), R65.2
unnamed: D5.2 (A), R66.2
unnamed: D6.2 (A), R67.2
unnamed: D7.2 (A), R68.2
unnamed: D8.2 (A), R69.2
unnamed: D9.2 (A), R70.2
unnamed: D10.2 (A), R71.2
unnamed: D12.2 (A), R73.2
unnamed: D13.2 (A), R74.2

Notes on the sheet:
RUN/STOP BUTTON

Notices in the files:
electronics/opensync/opensync.kicad_pcb:
OpenPIV © 2026
electronics/prototypes/opensync_prototype_4ch/opensync_prototype.kicad_pcb:
OpenPIV © 2025
